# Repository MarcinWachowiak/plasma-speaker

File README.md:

# Plasma-Speaker

https://hackaday.io/project/160041-plasma-speaker-exploring-properties-of-plasma

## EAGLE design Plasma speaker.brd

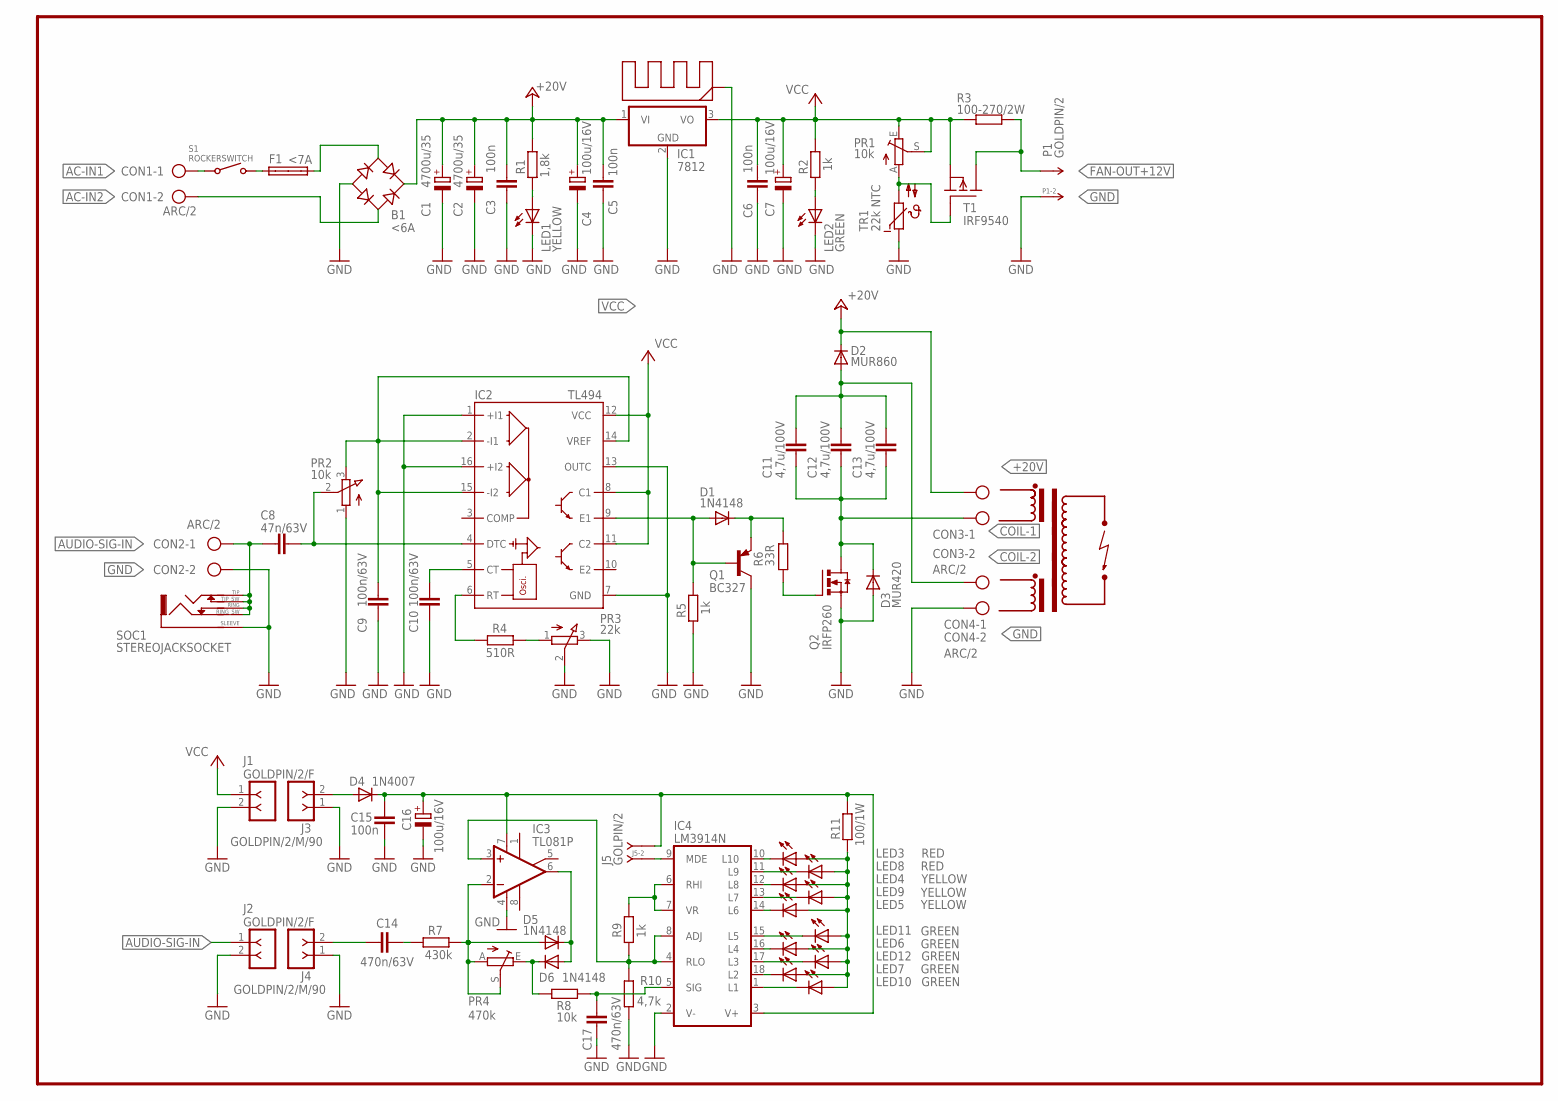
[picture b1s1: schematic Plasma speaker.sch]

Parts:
B1: <6A; SKB32
C1, C2: 4700u/35; E7,5-18
C3, C5, C6, C15: 100n; C025-025X050
C4, C7, C16: 100u/16V; E2,5-5
C8: 47n/63V; C050-025X075
C9, C10: 100n/63V; C050-025X075
C11, C12, C13: 4,7u/100V; C275-093X316
C14, C17: 470n/63V; C050-050X075
CON1, CON2, CON3, CON4: ARC/2; AK300/2
D1, D5, D6: 1N4148; DO35-7
D2: MUR860; TO220ACS
D3: MUR420; SGA-10
D4: 1N4007; DO41-10
F1: <7A; SHK20L
IC1: 7812; TO220V
IC2: TL494; DIL16
IC3: TL081P; DIL08
IC4: LM3914N; DIL18
J1, J2: GOLDPIN/2/F; SIP-100-02-40Y
J3, J4: GOLDPIN/2/M/90; KK-4455-A02
J5: GOLPIN/2; SIP-100-02-40Y
LED1, LED4, LED5, LED9: YELLOW; LED5MM
LED2, LED6, LED7, LED10, LED11, LED12: GREEN; LED5MM
LED3, LED8: RED; LED5MM
P1: GOLDPIN/2; SIP-100-02-40Y
PR1: 10k; CA6V
PR2: 10k; 3RP/1610N
PR3: 22k; 3RP/1610N
PR4: 470k; CA6V
Q1: BC327; TO92-EBC
Q2: IRFP260; TO247BV
R1: 1,8k; 0204/7
R2, R5, R9: 1k; 0204/7
R3: 100-270/2W; 0309/12
R4: 510R; 0204/7
R6: 33R; 0207/10
R7: 430k; 0204/7
R8: 10k; 0204/7
R10: 4,7k; 0204/7
R11: 100/1W; 0411/15
RAD1: TO3; RADIATOR
S1: ROCKERSWITCH; ROCKER
SOC1: STEREOJACKSOCKET; PICAXE_STEREOJACKSOCKET
T1: IRF9540; TO220
TR1: 22k NTC; P640

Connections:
+20V: B1.+, C1.+, C2.+, C3.1, C4.+, C5.1, CON3.1, D2.C, IC1.1 (VI), R1.1
AC-IN1: CON1.1, S1.IN1 (IN), S1.IN2 (IN)
AC-IN2: B1.AC2, CON1.2
AUDIO-SIG-IN: C8.2, CON2.1, J2.1, SOC1.RING, SOC1.RING_SW (RING-SW), SOC1.TIP, SOC1.TIP_SW (TIP-SW)
COIL-1: C11.2, C12.2, C13.2, CON3.2, D3.C, Q2.D
COIL-2: C11.1, C12.1, C13.1, CON4.1, D2.A
FAN-OUT+12V: P1.1, R3.2, T1.2 (D)
GND: B1.-, C1.-, C2.-, C3.2, C4.-, C5.2, C6.2, C7.-, C9.2, C10.2, C15.2, C16.-, C17.1, CON2.2, CON4.2, D3.A, IC1.2 (GND), IC2.1 (+I1), IC2.7 (GND), IC2.13 (OUTC), IC2.16 (+I2), IC3.4 (V-), IC4.2 (V-), J1.2, J2.2, J3.1, J4.1, LED1.K (C), LED2.K (C), P1.2, PR2.1 (A), PR3.2 (S), PR3.3 (E), Q1.C, Q2.S, R5.1, R10.2, RAD1.GND, SOC1.SLEEVE, TR1.1
unnamed: B1.AC1, F1.2A
unnamed: C14.1, J4.2
unnamed: C8.1, IC2.4 (DTC), PR2.2 (S)
unnamed: Q2.G, R6.1
unnamed: PR1.A, T1.1 (G), TR1.2
unnamed: D1.A, IC2.9 (E1), Q1.B, R5.2
unnamed: D4.A, J3.2
unnamed: IC4.10 (L10), LED3.K (C)
unnamed: C10.1, IC2.5 (CT)
unnamed: IC2.6 (RT), R4.2
unnamed: PR3.1 (A), R4.1
unnamed: D1.C, Q1.E, R6.2
unnamed: F1.1A, S1.OUT
unnamed: LED2.A, R2.2
unnamed: LED1.A, R1.2
unnamed: C9.1, IC2.2 (-I1), IC2.14 (VREF), IC2.15 (-I2), PR2.3 (E)
unnamed: IC4.11 (L9), LED8.K (C)
unnamed: IC4.12 (L8), LED4.K (C)
unnamed: IC4.13 (L7), LED9.K (C)
unnamed: IC4.14 (L6), LED5.K (C)
unnamed: IC4.1 (L1), LED10.K (C)
unnamed: IC4.18 (L2), LED7.K (C)
unnamed: IC4.17 (L3), LED12.K (C)
unnamed: IC4.16 (L4), LED6.K (C)
unnamed: IC4.15 (L5), LED11.K (C)
unnamed: LED3.A, LED4.A, LED5.A, LED6.A, LED7.A, LED8.A, LED9.A, LED10.A, LED11.A, LED12.A, R11.1
unnamed: IC3.3 (+IN), IC4.4 (RLO), IC4.8 (ADJ), R9.2, R10.1
unnamed: D5.A, IC3.2 (-IN), PR4.A, PR4.S, R7.1
unnamed: IC4.6 (RHI), IC4.7 (VR), R9.1
unnamed: C14.2, R7.2
unnamed: D5.C, D6.A, IC3.6 (OUT)
unnamed: IC4.9 (MDE), J5.2
unnamed: D6.C, PR4.E, R8.2
unnamed: C17.2, IC4.5 (SIG), R8.1
V+: C15.1, C16.+, D4.C, IC3.7 (V+), IC4.3 (V+), J5.1, R11.2
VCC: C6.1, C7.+, IC1.3 (VO), IC2.8 (C1), IC2.11 (C2), IC2.12 (VCC), J1.1, PR1.E, PR1.S, R2.1, R3.1, T1.3 (S)

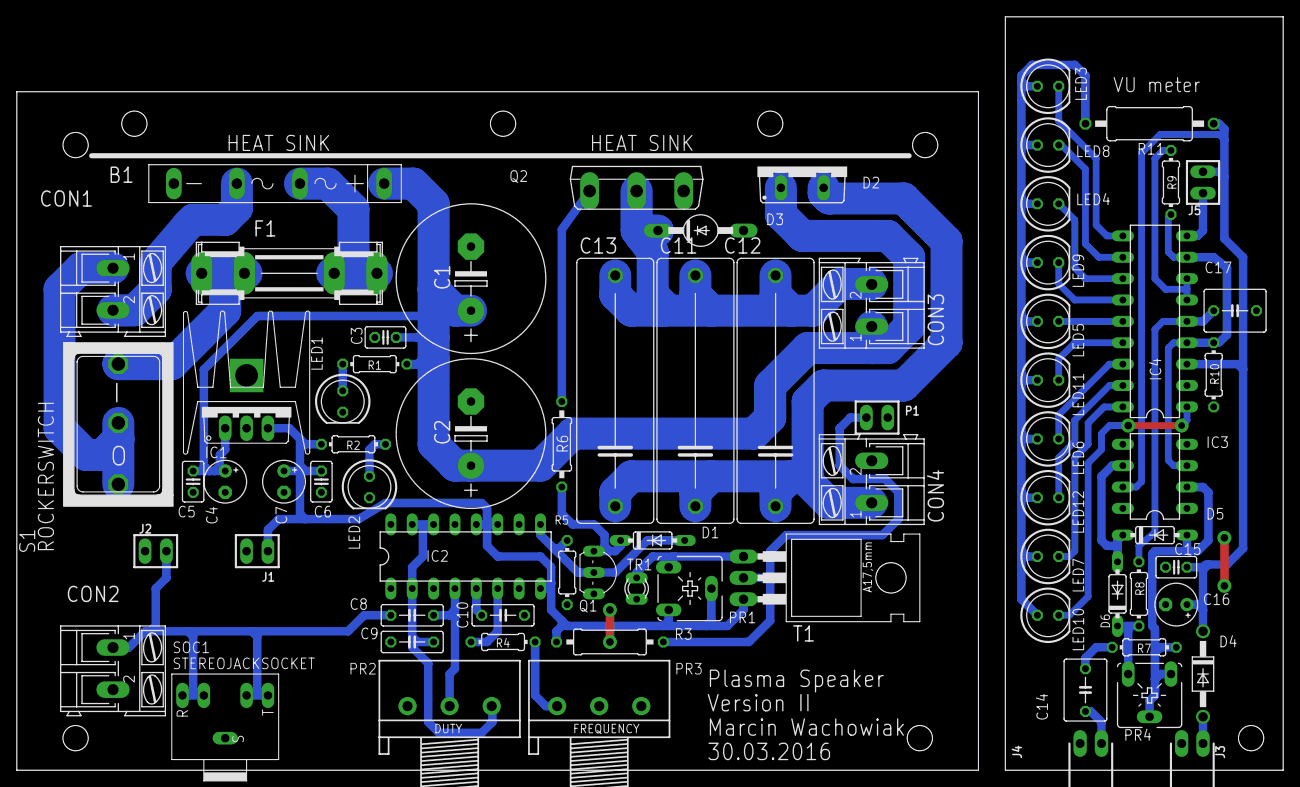
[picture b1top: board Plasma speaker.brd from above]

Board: 2 copper layers, 150.4 x 89.4 mm, 73 parts (0 on the bottom side), 44 nets.

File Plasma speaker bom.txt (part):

Partlist exported from F:/Projekty/Finished_to_be_published/Plasma_speaker/Github/Plasma speaker.sch at 29.07.2018 18:45

Part  Value            Device                  Package                 Description                                                     
B1    <6A              RECTIFIER-SKB32         SKB32                   Rectifier                                                       
C1    4700u/35         CPOL-EUE7.5-18          E7,5-18                 POLARIZED CAPACITOR, European symbol                            
C2    4700u/35         CPOL-EUE7.5-18          E7,5-18                 POLARIZED CAPACITOR, European symbol                            
C3    100n             C-EU025-025X050         C025-025X050            CAPACITOR, European symbol                                      
C4    100u/16V         CPOL-EUE2.5-5           E2,5-5                  POLARIZED CAPACITOR, European symbol                            
C5    100n             C-EU025-025X050         C025-025X050            CAPACITOR, European symbol                                      
C6    100n             C-EU025-025X050         C025-025X050            CAPACITOR, European symbol                                      
C7    100u/16V         CPOL-EUE2.5-5           E2,5-5                  POLARIZED CAPACITOR, European symbol                            
C8    47n/63V          C-EU050-025X075         C050-025X075            CAPACITOR, European symbol                                      
C9    100n/63V         C-EU050-025X075         C050-025X075            CAPACITOR, European symbol                                      
C10   100n/63V         C-EU050-025X075         C050-025X075            CAPACITOR, European symbol                                      
C11   4,7u/100V        C-EU275-093X316         C275-093X316            CAPACITOR, European symbol                                      
C12   4,7u/100V        C-EU275-093X316         C275-093X316            CAPACITOR, European symbol                                      
C13   4,7u/100V        C-EU275-093X316         C275-093X316            CAPACITOR, European symbol                                      
C14   470n/63V         C-EU050-050X075         C050-050X075            CAPACITOR, European symbol                                      
C15   100n             C-EU025-025X050         C025-025X050            CAPACITOR, European symbol                                      
C16   100u/16V         CPOL-EUE2.5-5           E2,5-5                  POLARIZED CAPACITOR, European symbol                            
C17   470n/63V         C-EU050-050X075         C050-050X075            CAPACITOR, European symbol                                      
CON1  ARC/2            AK300/2                 AK300/2                 CONNECTOR                                                       
CON2  ARC/2            AK300/2                 AK300/2                 CONNECTOR                                                       
CON3  ARC/2            AK300/2                 AK300/2                 CONNECTOR                                                       
CON4  ARC/2            AK300/2                 AK300/2                 CONNECTOR                                                       
D1    1N4148           1N4148DO35-7            DO35-7                  DIODE                                                           
D2    MUR860           BYT08P                  TO220ACS                DIODE                                                           
D3    MUR420           BY203                   SGA-10                  DIODE                                                           
D4    1N4007           1N4004                  DO41-10                 DIODE                                                           
D5    1N4148           1N4148DO35-7            DO35-7                  DIODE                                                           
D6    1N4148           1N4148DO35-7            DO35-7                  DIODE                                                           
F1    <7A              SHK20L                  SHK20L                  FUSE HOLDER 5 x 20 mm, SH contact, SHH1 Schukat, E1073 Buerklin 
IC1   7812             7812TV                  TO220V                  Positive VOLTAGE REGULATOR                                      
IC2   TL494            TL494CN                 DIL16                   SWITCHMODE Pulse Width Modulation Control Circuit               
IC3   TL081P           TL081P                  DIL08                   OP AMP                                                          
IC4   LM3914N          LM3914N                 DIL18                   LED DRIVER                                                      
J1    GOLDPIN/2/F      F-1X02-SIP-100-40Y      SIP-100-02-40Y          FEMALE HEADER                                                   
J2    GOLDPIN/2/F      F-1X02-SIP-100-40Y      SIP-100-02-40Y          FEMALE HEADER                                                   
J3    GOLDPIN/2/M/90   F-1X02-KK-4455-A02      KK-4455-A02             FEMALE HEADER                                                   
J4    GOLDPIN/2/M/90   F-1X02-KK-4455-A02      KK-4455-A02             FEMALE HEADER                                                   
J5    GOLPIN/2         J-02-SIP-100-40Y        SIP-100-02-40Y          HEADER JACK PINS                                                
LED1  YELLOW           LED5MM                  LED5MM                  LED                                                             
LED2  GREEN            LED5MM                  LED5MM                  LED                                                             
LED3  RED              LED5MM                  LED5MM                  LED                                                             
LED4  YELLOW           LED5MM                  LED5MM                  LED                                                             
LED5  YELLOW           LED5MM                  LED5MM                  LED                                                             
LED6  GREEN            LED5MM                  LED5MM                  LED                                                             
LED7  GREEN            LED5MM                  LED5MM                  LED                                                             
LED8  RED              LED5MM                  LED5MM                  LED                                                             
LED9  YELLOW           LED5MM                  LED5MM                  LED                                                             
LED10 GREEN            LED5MM                  LED5MM                  LED                                                             
LED11 GREEN            LED5MM                  LED5MM                  LED                                                             
LED12 GREEN            LED5MM                  LED5MM                  LED                                                             
P1    GOLDPIN/2        P-02-SIP-100-40Y        SIP-100-02-40Y          HEADER PLUG PINS                                                
PR1   10k              TRIM_EU-CA6V            CA6V                    POTENTIOMETER                                                   
PR2   10k              3RP/1610N               3RP/1610N               16mm Potentiometer one level                                    
PR3   22k              3RP/1610N               3RP/1610N               16mm Potentiometer one level                                    
PR4   470k             TRIM_EU-CA6V            CA6V                    POTENTIOMETER                                                   
Q1    BC327            BC327-25-PNP-TO92-EBC   TO92-EBC                PNP Transistror                                                 
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
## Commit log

2018-07-29 Added Eagle sch/brd and description files

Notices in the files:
parts and their libraries:
con-headers-jp: Copyright (C) 2008, Bob Starr
